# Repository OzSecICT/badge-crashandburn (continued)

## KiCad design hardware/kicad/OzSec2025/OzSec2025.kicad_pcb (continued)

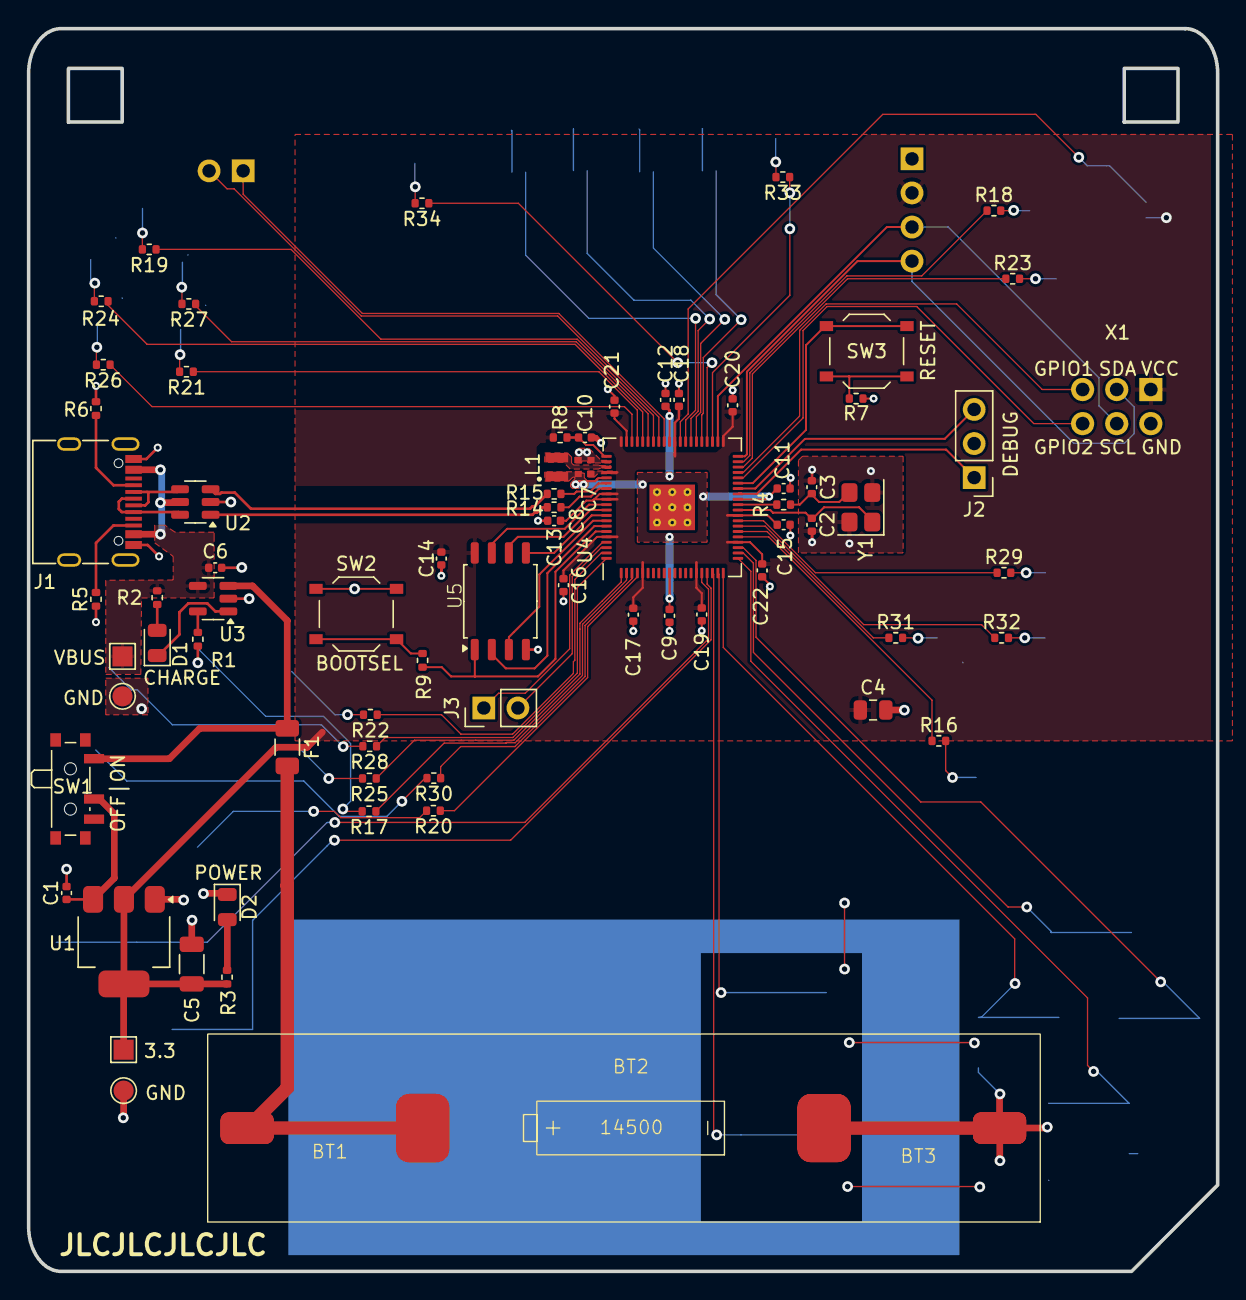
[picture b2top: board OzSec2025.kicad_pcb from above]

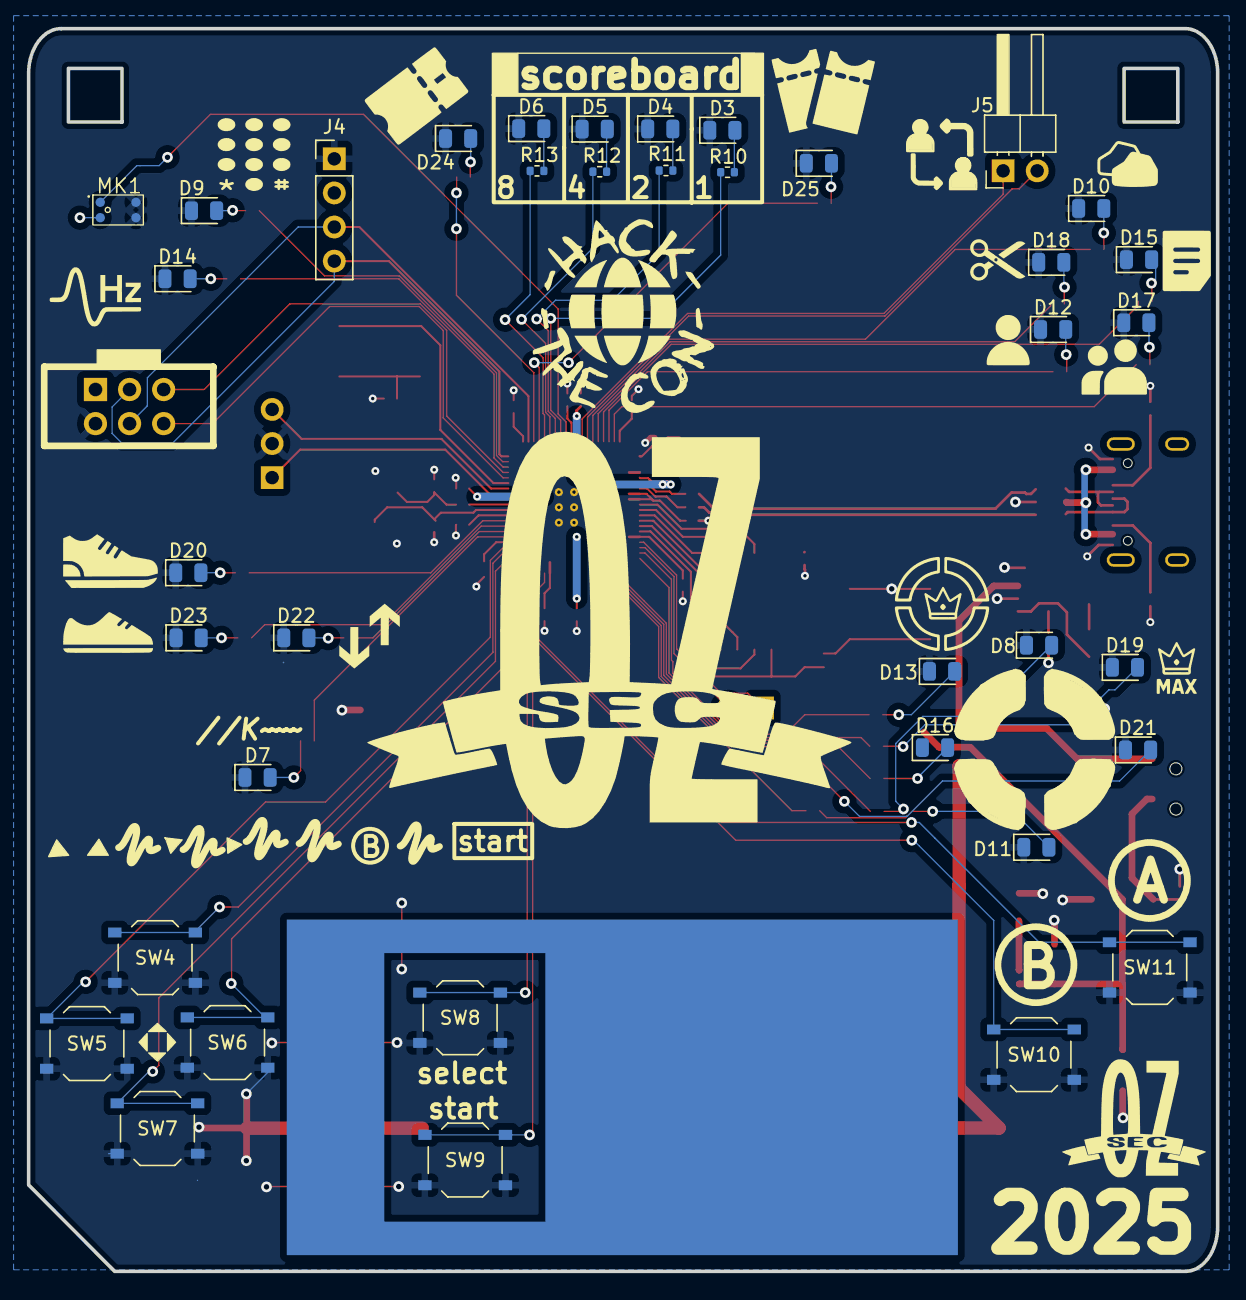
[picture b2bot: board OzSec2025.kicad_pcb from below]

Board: 2 copper layers, 88.6 x 92.6 mm, 114 parts (39 on the bottom side), 96 nets.

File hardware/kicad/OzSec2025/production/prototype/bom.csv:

Designator,Footprint,Quantity,Value,LCSC Part #
BT1,MY-AA-04_BT1A,1,Battery_Clip_+,
BT2,MY-AA-04,1,Battery,C2979179
BT3,MY-AA-04_BT1B,1,Battery_Clip_-,
"C1, C12, C13, C14, C15, C16, C17, C18, C19, C20, C21, C22, C9",0402,13,100n,C1525
"C10, C11, C7, C8",0402,4,4.7u,C23733
"C2, C3",0402,2,15p,C1548
C4,0805,1,10u,C15850
C5,1206,1,100uF,C15008
C6,0402,1,1uF,C52923
D1,0805,1,YELLOW,C2296
"D10, D11, D12, D13, D14, D15, D16, D17, D18, D19, D20, D21, D22, D23, D24, D25, D3, D4, D5, D6, D7, D8, D9",0805,23,WHITE,C34499
D2,0805,1,GREEN,C2297
F1,1206,1,Fuse,C261957
J1,USB_C_Receptacle_G-Switch_GT-USB-7010ASV,1,USB_C_Receptacle_USB2.0,C2988369
J5,PinHeader_1x02_P2.54mm_Horizontal,1,Conn_01x02,C492410
L1,L_pol_2016,1,3.3u,C42411119
MK1,LMA3722T421-OA5,1,LMA3722T421-OA5,C5373233
R1,0402,1,2K,C4109
"R10, R11, R12, R13, R16, R17, R18, R19, R2, R20, R21, R22, R23, R24, R25, R26, R27, R28, R29, R3, R30, R31, R32, R33, R34, R4, R7, R9",0402,28,1K,C11702
"R14, R15",0402,2,27,C25100
"R5, R6",0402,2,5.1K,C25905
R8,0402,1,33,C25105
SW1,SW_SPDT_PCM12,1,POWER,C431541
"SW10, SW11, SW2, SW3, SW4, SW5, SW6, SW7, SW8, SW9",SW_Push_1P1T_XKB_TS-1187A,10,SW_Push,C318884
"TP1, TP3",TestPoint_Pad_1.5x1.5mm,2,TestPoint,
"TP2, TP4",TestPoint_Pad_D1.5mm,2,TestPoint,
U1,SOT-223-3_TabPin2,1,TLV1117LV-33,C15578
U2,SOT-23-6,1,USBLC6-2SC6,C2827654
U3,TSOT-23-5,1,ME4054BM5G-N,C478383
U4,RP2350-QFN-80-1EP_10x10_P0.4mm_EP3.4x3.4mm_ThermalVias,1,RP2350_80QFN,C42415655
U5,SOIC-8_5.23x5.23mm_P1.27mm,1,W25Q128JVS,C97521
X1,Simple_Addon_v2-BADGE-2x3,1,Simple_Addon_v2,C2935983
Y1,Crystal_SMD_3225-4Pin_3.2x2.5mm,1,ABM8-272-T3,C20625731

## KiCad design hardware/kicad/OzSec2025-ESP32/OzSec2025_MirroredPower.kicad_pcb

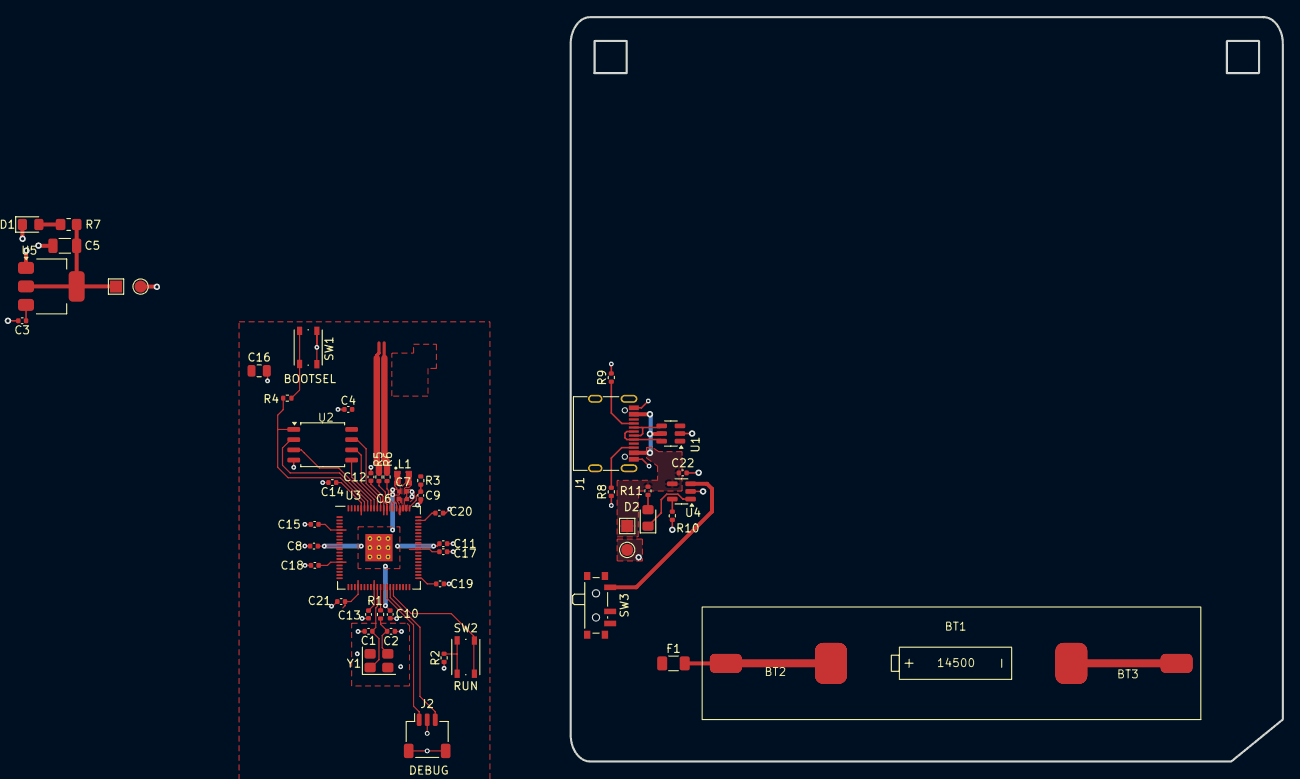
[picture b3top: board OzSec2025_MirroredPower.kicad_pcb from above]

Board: 2 copper layers, 88.6 x 92.6 mm, 55 parts (0 on the bottom side), 34 nets.

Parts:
BT1: Battery; MY-AA-04
BT2: Battery_Clip_+; MY-AA-04_BT1A
BT3: Battery_Clip_-; MY-AA-04_BT1B
C1, C2: 15p; C_0402_1005Metric
C3: 0.1uF; C_0402_1005Metric
C4, C8, C11, C12, C13, C14, C15, C17, C18, C19, C20, C21: 100n; C_0402_1005Metric
C5: 100uF; C_1206_3216Metric
C6, C7: 4.7u; C_0402_1005Metric_small_pads
C9, C10: 4.7u; C_0402_1005Metric
C16: 10u; C_0805_2012Metric
C22: 1uF; C_0402_1005Metric
D1: POWER; LED_0805_2012Metric_Pad1.15x1.40mm_HandSolder
D2: CHARGING; LED_0805_2012Metric_Pad1.15x1.40mm_HandSolder
F1: Fuse; Fuse_1206_3216Metric
J1: USB_C_Receptacle_USB2.0; USB_C_Receptacle_G-Switch_GT-USB-7010ASV
J2: SM03B-SRSS-TB; JST_SH_SM03B-SRSS-TB_1x03-1MP_P1.00mm_Horizontal
L1: 3.3u; L_pol_2016
R1, R2, R4: 1k; R_0402_1005Metric
R3: 33; R_0402_1005Metric
R5, R6: 27; R_0402_1005Metric
R7: 1K; R_0805_2012Metric_Pad1.20x1.40mm_HandSolder
R8, R9: 5.1K; R_0402_1005Metric
R10: 2K; R_0402_1005Metric
R11: 1K; R_0402_1005Metric
SW1, SW2: SW_Push; SW_Push_1P1T_NO_Vertical_Wuerth_434133025816
SW3: POWER; SW_SPDT_PCM12
TP1, TP3: TestPoint; TestPoint_Pad_1.5x1.5mm
TP2, TP4: TestPoint; TestPoint_Pad_D1.5mm
U1: USBLC6-2SC6; SOT-23-6
U2: W25Q128JVS; SOIC-8_5.23x5.23mm_P1.27mm
U3: RP2350_80QFN; RP2350-QFN-80-1EP_10x10_P0.4mm_EP3.4x3.4mm_ThermalVias
U4: ME4054BM5G-N; TSOT-23-5
U5: TLV1117LV-33; SOT-223-3_TabPin2
Y1: ABM8-272-T3; Crystal_SMD_3225-4Pin_3.2x2.5mm

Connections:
+1V1: C7.1, C8.1, C10.1, C11.1, L1.1, U3.10 (DVDD), U3.32 (DVDD), U3.51 (DVDD), U3.65 (VREG_FB)
+3.3V: C5.1, R7.1, TP3.1, U5.2 (VO)
+3V3: C4.1, C6.1, C12.1, C13.1, C14.1, C15.1, C16.1, C17.1, C18.1, C19.1, C20.1, C21.1, R3.1, U2.8 (VCC), U3.5 (IOVDD), U3.15 (IOVDD), U3.24 (IOVDD), U3.29 (IOVDD), U3.41 (IOVDD), U3.50 (IOVDD), U3.59 (ADC_AVDD), U3.60 (IOVDD), U3.64 (VREG_VIN), U3.68 (USB_OTP_VDD), U3.69 (QSPI_IOVDD), U3.76 (IOVDD)
+BATT: C3.1, SW3.2 (B), U5.3 (VI)
/QSPI_SCLK: U2.6 (CLK), U3.71 (QSPI_SCLK)
/QSPI_SD0: U2.5 (DI(IO0)), U3.72 (QSPI_SD0)
/QSPI_SD1: U2.2 (DO(IO1)), U3.74 (QSPI_SD1)
/QSPI_SD2: U2.3 (IO2), U3.73 (QSPI_SD2)
/QSPI_SD3: U2.7 (IO3), U3.70 (QSPI_SD3)
/QSPI_SS: R4.1, U2.1 (~CS), U3.75 (QSPI_SS)
/RUN: SW2.2, U3.35 (RUN)
/SWCLK: J2.1, U3.33 (SWCLK)
/SWD: J2.3, U3.34 (SWD)
/USB_D+: J1.A6 (D+), J1.B6 (D+), R5.1, U1.1 (I/O1), U1.6 (I/O1)
/USB_D-: J1.A7 (D-), J1.B7 (D-), R6.1, U1.3 (I/O2), U1.4 (I/O2)
/VREG_AVDD: C9.1, R3.2, U3.61 (VREG_AVDD)
/VREG_LX: L1.2, U3.63 (VREG_LX)
/XIN: C1.1, U3.30 (XIN), Y1.1
/XOUT: R1.1, U3.31 (XOUT)
/~USB_BOOT: R4.2, SW1.2
GND: BT1.2 (-), BT3.1, C1.2, C2.2, C3.2, C4.2, C5.2, C6.2, C7.2, C8.2, C9.2, C10.2, C11.2, C12.2, C13.2, C14.2, C15.2, C16.2, C17.2, C18.2, C19.2, C20.2, C21.2, C22.2, D1.1 (K), J1.A1 (GND), J1.A12 (GND), J1.B1 (GND), J1.B12 (GND), J2.2, J2.MP (MountPin), R2.2, R8.1, R9.2, R10.2, SW1.1, TP2.1, TP4.1, U1.2 (GND), U2.4 (GND), U3.62 (VREG_PGND), U3.81 (GND), U4.2 (GND), U5.1 (GND), Y1.2, Y1.4
unnamed: BT1.1 (+), BT2.1, F1.2
unnamed: C2.1, R1.2, Y1.3
unnamed: D1.2 (A), R7.2
unnamed: D2.2 (A), R11.2
unnamed: D2.1 (K), U4.1 (~CHRG)
unnamed: J1.A5 (CC1), R9.1
unnamed: J1.B5 (CC2), R8.2
unnamed: R2.1, SW2.1
unnamed: F1.1, SW3.1 (A), U4.3 (BAT)
unnamed: R6.2, U3.66 (USB_DM)
unnamed: R5.2, U3.67 (USB_DP)
unnamed: R10.1, U4.5 (PROG)
VBUS: C22.1, J1.A4 (VBUS), J1.A9 (VBUS), J1.B4 (VBUS), J1.B9 (VBUS), R11.1, TP1.1, U1.5 (VBUS), U4.4 (V_{CC})

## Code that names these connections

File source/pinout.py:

"""
Pinout configuration

Defines pins for prototyping and production. Prototype versions used a Pico 2
which does not have enough GPIO available for all games.

Prototype_1: Missing I2C, SAO GPIO, Simon, and DTMF games
Prototype_2: Missing I2C, SAO GPIO, HiLo and RPS game.
Production: All pins available.
"""
from machine import Pin

pinout_type = "production"

print(f"Using pinout type: {pinout_type}")


if pinout_type == "production":
    # Controller inputs
    pin_button_a = 12
    pin_button_b = 13
    pin_button_select = 14
    pin_button_start = 21
    pin_dpad_right = 47
    pin_dpad_down = 48
    pin_dpad_up = 38
    pin_dpad_left = 45

    # Scoreboard
    pin_score_eights = 15
    pin_score_fours = 7
    pin_score_twos = 6
    pin_score_ones = 5

    # Badge/Raffle LEDs
    pin_badge_complete = 2
    pin_badge_bonus = 4

    # Game LEDs
    pin_simon_complete = 46
    pin_simon_left = 11
    pin_simon_up = 3
    pin_simon_down = 10
    pin_simon_right = 9

    pin_kode_complete = 39

    pin_hilo_complete = 40
    pin_hilo_lo = 41
    pin_hilo_hi = 42

    pin_dtmf_bonus = 44
    pin_dtmf_complete = 43
    pin_dtmf_mic = 1

    pin_rps_rock = 16
    pin_rps_scissors = 18
    pin_rps_paper = 17
    pin_rps_complete = 8

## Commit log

2025-02-02 Add gitignore
2025-02-06 Initial folder structure and supporting files.
2025-02-06 Typo
2025-02-06 Fixed README
2025-02-07 Add Pico 2 pinout for reference.
2025-02-08 WIP for PIN's
2025-02-09 Breadboard config for buttons and leds.
2025-02-09 Initial game attempt.
2025-02-14 Fixed upload vs code task.
2025-02-15 Moved DebouncedInput to button.py and added clear function.
2025-02-15 Added flash, toggle and clear functions.
2025-02-15 Game changes.
2025-02-15 Game class.
2025-02-15 WIP moving to game class.
2025-02-15 Light game working as class.
2025-02-15 Moved to class based mini-games.
2025-02-16 Added comments to stop pylance complaining.
2025-03-12 Added ignore comments for linting.
2025-03-12 Added/moved datasheets
2025-03-12 Initial DTMF game, WIP
2025-04-19 Added notes
2025-04-19 Updated gitignore with kicad stuff
2025-04-19 Initial work on pcb routing
2025-04-19 Update kicad libraries and initial work on routing.
2025-04-19 Update footprints
2025-04-19 Clean slate on PCB.
2025-06-21 Removed outdated kicad files, and added some new ones.
2025-06-21 Added kicad files.
2025-06-22 Updated git ignore
2025-06-22 Add debug and cleanup game.py
2025-06-22 Blink and ability to pause/resume timers
2025-06-22 Created scoreboard
2025-06-22 Accepted copilot code review changes.
2025-06-23 Added pinout definitions to support prototype testing with limited gpio
2025-06-24 Added brightness memory for PWM.
2025-06-24 Added debug prints.
2025-06-24 Added default select function
2025-06-24 Updated games and added idle led mode toggle.
2025-06-24 Add flag.
2025-06-26 Added flag
2025-06-26 Game cleanup
2025-06-26 Idle blinky and some fixes.
2025-06-26 Added threading for handling idle blink state. Needs some more work.
2025-06-26 Added scoreboard support. Also added flash nuke firmware from Raspberry Pi to wipe a Pico.
2025-06-26 Updated gitignore.
2026-01-05 Added fabrication files for v1.2
2026-01-05 Added esp32 firmware
2026-01-05 Updated kicad files
2026-01-05 Added datasheets
2026-01-05 ESP32 updates, functional blinky
